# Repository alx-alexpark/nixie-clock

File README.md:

# ИН-12 Nixie Tube Clock

A nixie tube clock made using ИН-12 (IN-12) tubes. Uses k155id1 drivers and a boost converter made using [this reference design](https://github.com/drkmsmithjr/NixiePowerSupply). Time is synchronized over WiFi using NTP (<1sec inaccuracy), and all firmware is written using CircuitPython.

Read more at https://parkalex.dev/posts/nixieclock

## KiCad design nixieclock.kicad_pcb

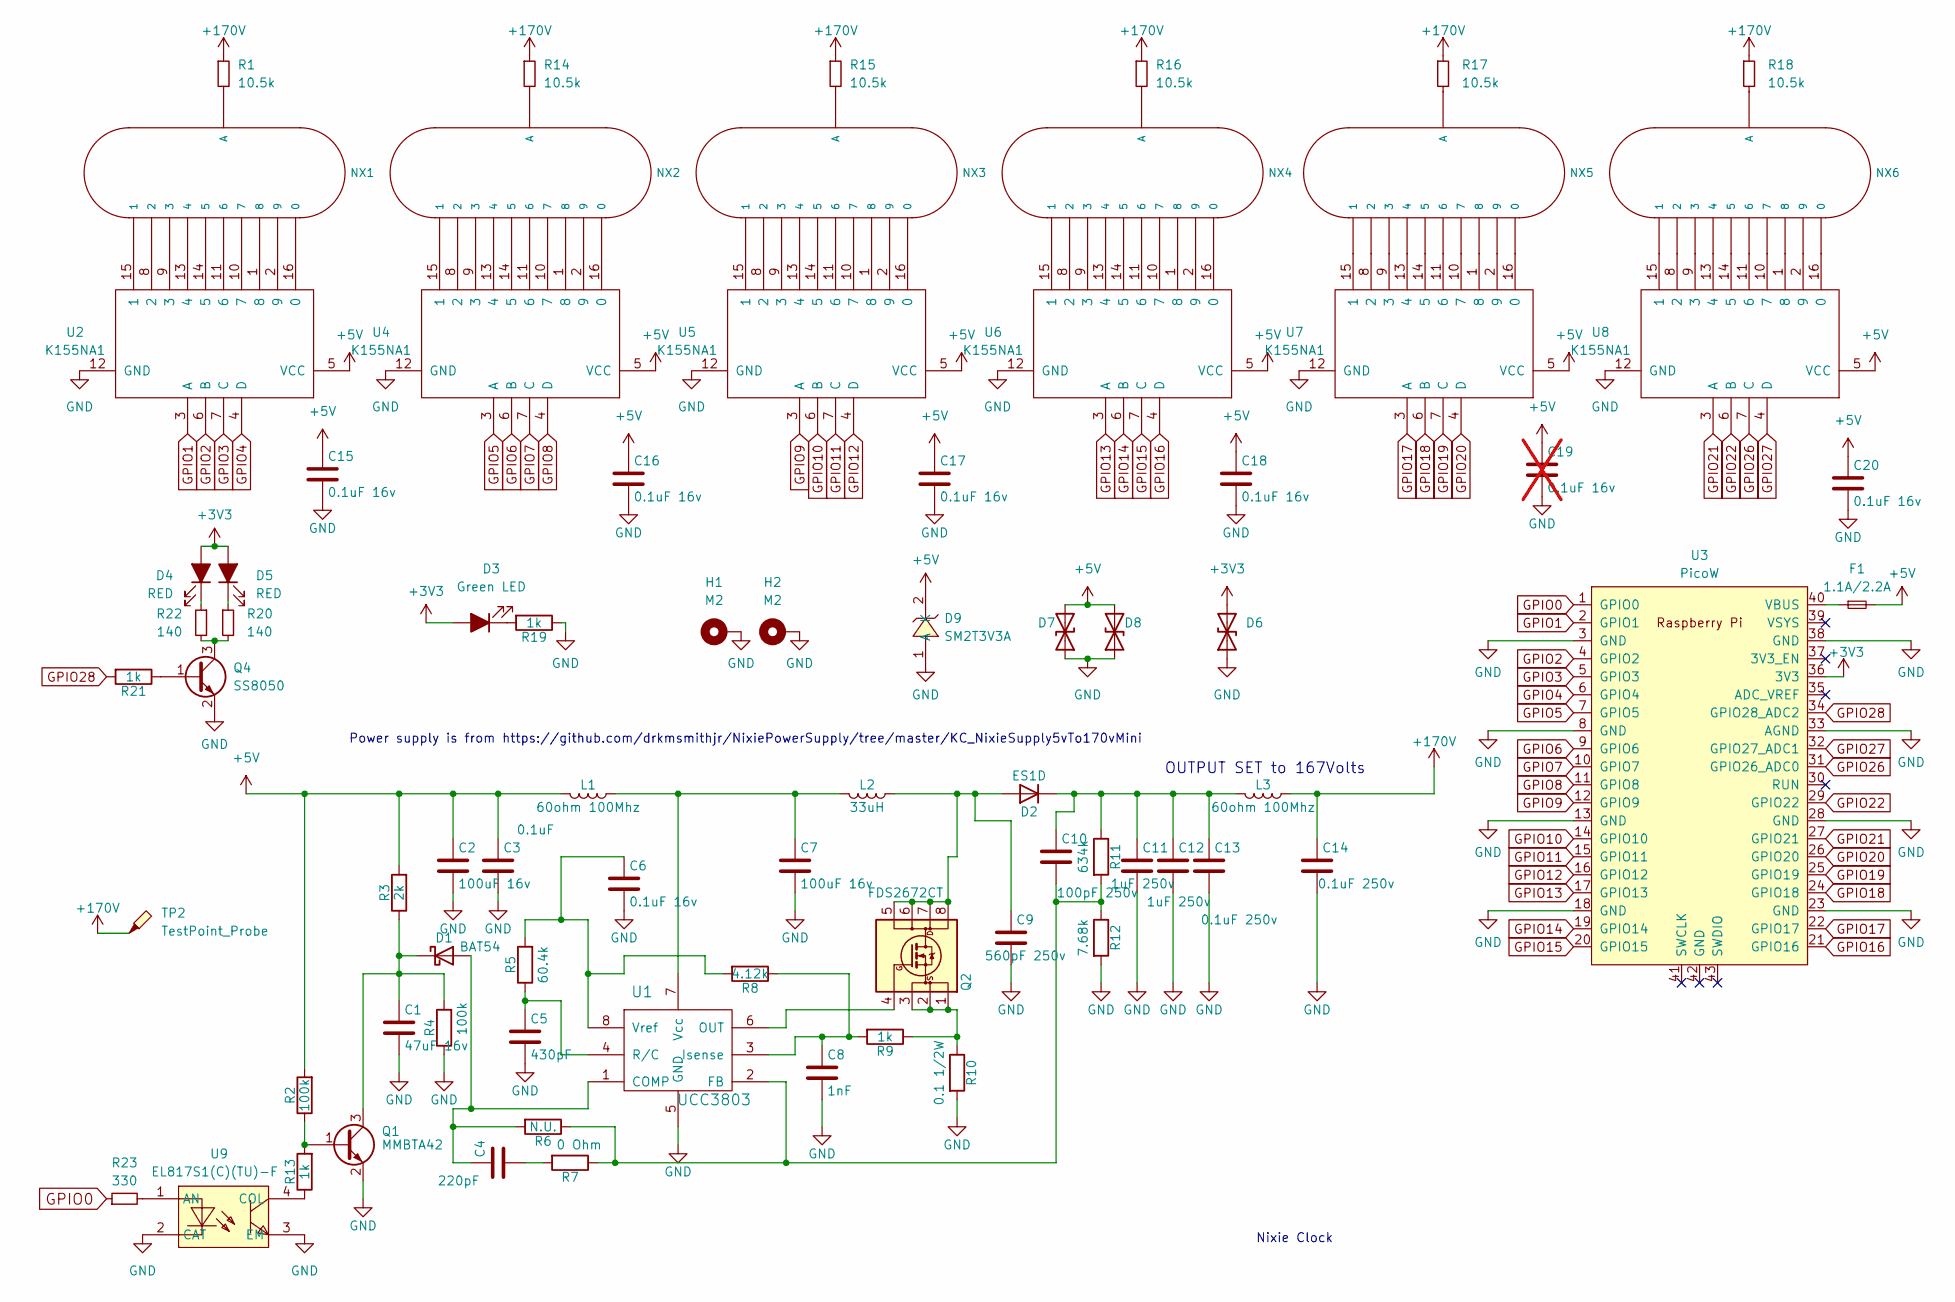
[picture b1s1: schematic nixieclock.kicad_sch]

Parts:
C1: 47uF 16v; C_1210_3225Metric_Pad1.33x2.70mm_HandSolder; LCSC Part C77101
C2, C7: 100uF 16v; C_1210_3225Metric_Pad1.33x2.70mm_HandSolder; LCSC Part C7432790
C3: 0.1uF; C_0603_1608Metric_Pad1.08x0.95mm_HandSolder; LCSC Part C14663
C4: 220pF; C_0402_1005Metric_Pad0.74x0.62mm_HandSolder; LCSC Part C1530
C5: 430pF; C_0805_2012Metric_Pad1.18x1.45mm_HandSolder; LCSC Part C67898
C6, C15, C16, C17, C18, C20: 0.1uF 16v; C_0603_1608Metric_Pad1.08x0.95mm_HandSolder; LCSC Part C14663
C8: 1nF; C_0603_1608Metric_Pad1.08x0.95mm_HandSolder; LCSC Part C100040
C9: 560pF 250v; C_0805_2012Metric_Pad1.18x1.45mm_HandSolder; LCSC Part C576987
C10: 100pF 250v; C_0805_2012Metric_Pad1.18x1.45mm_HandSolder; LCSC Part C5186766
C11, C12: 1uF 250v; C_1812_4532Metric_Pad1.57x3.40mm_HandSolder; LCSC Part C381468
C13, C14: 0.1uF 250v; C_0805_2012Metric_Pad1.18x1.45mm_HandSolder; LCSC Part C5182461
C19: 0.1uF 16v; C_0603_1608Metric_Pad1.08x0.95mm_HandSolder; LCSC Part C14663; not fitted
D1: BAT54; D_SOD-323_HandSoldering; MPN BAT54WS-7-F; LCSC Part C124205
D2: ES1D; D_SMA_Handsoldering; MPN ES1D; LCSC Part C84602
D3: Green LED; LED_0805_2012Metric_Pad1.15x1.40mm_HandSolder; LCSC Part C2297
D4, D5: RED; LED_0805_2012Metric_Pad1.15x1.40mm_HandSolder; LCSC Part C84256
D6, D7, D8: PESD5V5C1BLYL; D_SOD-882; MPN PESD5V5C1BLYL
D9: SM2T3V3A; DO-216AA_L1.9-W1.9-LS3.8-FD; LCSC Part C970557
F1: 1.1A/2.2A; Fuse_1812_4532Metric_Pad1.30x3.40mm_HandSolder; MPN MF-MSMF110-2
H1, H2: M2; MountingHole_2.2mm_M2_DIN965_Pad_TopBottom
L1, L3: 60ohm 100Mhz; L_0805_2012Metric_Pad1.05x1.20mm_HandSolder; MPN MH2029-600Y
L2: 33uH; WE-PD_1210; MPN 7447709330
NX1, NX2, NX3, NX4, NX5, NX6: IN-12A; nixies-us-IN-12-DSUB
Q1: MMBTA42; SOT-23_Handsoldering; LCSC Part C118745
Q2: FDS2672CT; SOIC-8_3.9x4.9mm_P1.27mm; MPN FDS2672CT-ND
Q4: SS8050; SOT-23
R1, R14, R15, R16, R17, R18: 10.5k; R_0805_2012Metric_Pad1.20x1.40mm_HandSolder; LCSC Part C2093736
R2, R4: 100k; R_0603_1608Metric_Pad0.98x0.95mm_HandSolder; LCSC Part C14675
R3: 2k; R_0603_1608Metric_Pad0.98x0.95mm_HandSolder; LCSC Part C22975
R5: 60.4k; R_0603_1608Metric_Pad0.98x0.95mm_HandSolder; LCSC Part C23089
R6: N.U.
R7: 0 Ohm; R_0603_1608Metric_Pad0.98x0.95mm_HandSolder; LCSC Part C21189
R8: 4.12k; R_0603_1608Metric_Pad0.98x0.95mm_HandSolder; LCSC Part C2960702
R9, R13, R19, R21: 1k; R_0603_1608Metric_Pad0.98x0.95mm_HandSolder; LCSC Part C21190
R10: 0.1 1/2W; C_1210_3225Metric_Pad1.33x2.70mm_HandSolder; LCSC Part C2974119
R11: 634k; R_1206_3216Metric_Pad1.30x1.75mm_HandSolder; LCSC Part C3037408
R12: 7.68k; R_1206_3216Metric_Pad1.30x1.75mm_HandSolder; LCSC Part C3037264
R20, R22: 140; R_0603_1608Metric_Pad0.98x0.95mm_HandSolder; LCSC Part C2974027
R23: 330; R_0603_1608Metric_Pad0.98x0.95mm_HandSolder; LCSC Part C23138
TP2: TestPoint_Probe; TestPoint_Loop_D2.54mm_Drill1.5mm_Beaded
U1: UCC3803; SOIC-8_3.9x4.9mm_P1.27mm; LCSC Part C2657971
U2, U4, U5, U6, U7, U8: K155NA1; DIP-16_W7.62mm_LongPads
U3: PicoW; RPi_PicoW_SMD_TH
U9: EL817S1(C)(TU)-F; OPTO-SMD-4_L4.6-W6.5-P2.54-LS10.3-TL; LCSC Part C106900

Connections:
+3V3: D3.2 (A), D4.2 (A), D5.2 (A), D6.2 (A2), U3.36 (3V3)
+5V: C2.1, C3.1, C15.1, C16.1, C17.1, C18.1, C19.1, C20.1, D7.2 (A2), D8.2 (A2), D9.2 (K), F1.2, L1.2, R2.2, R3.2, U2.5 (VCC), U4.5 (VCC), U5.5 (VCC), U6.5 (VCC), U7.5 (VCC), U8.5 (VCC)
+170V: C14.1, L3.1, R1.1, R14.1, R15.1, R16.1, R17.1, R18.1, TP2.1
GND: C1.2, C2.2, C3.2, C5.2, C6.2, C7.2, C8.2, C9.2, C11.2, C12.2, C13.2, C14.2, C15.2, C16.2, C17.2, C18.2, C19.2, C20.2, D6.1 (A1), D7.1 (A1), D8.1 (A1), D9.1 (A), H1.1, H2.1, Q1.2 (E), Q4.2 (E), R4.1, R10.2, R12.2, R19.1, U1.5 (GND), U2.12 (GND), U3.3 (GND), U3.8 (GND), U3.13 (GND), U3.18 (GND), U3.23 (GND), U3.28 (GND), U3.33 (AGND), U3.38 (GND), U4.12 (GND), U5.12 (GND), U6.12 (GND), U7.12 (GND), U8.12 (GND), U9.2 (CAT), U9.3 (EM)
GPIO0: R23.1, U3.1 (GPIO0)
GPIO1: U2.3 (A), U3.2 (GPIO1)
GPIO2: U2.6 (B), U3.4 (GPIO2)
GPIO3: U2.7 (C), U3.5 (GPIO3)
GPIO4: U2.4 (D), U3.6 (GPIO4)
GPIO5: U3.7 (GPIO5), U4.3 (A)
GPIO6: U3.9 (GPIO6), U4.6 (B)
GPIO7: U3.10 (GPIO7), U4.7 (C)
GPIO8: U3.11 (GPIO8), U4.4 (D)
GPIO9: U3.12 (GPIO9), U5.3 (A)
GPIO10: U3.14 (GPIO10), U5.6 (B)
GPIO11: U3.15 (GPIO11), U5.7 (C)
GPIO12: U3.16 (GPIO12), U5.4 (D)
GPIO13: U3.17 (GPIO13), U6.3 (A)
GPIO14: U3.19 (GPIO14), U6.6 (B)
GPIO15: U3.20 (GPIO15), U6.7 (C)
GPIO16: U3.21 (GPIO16), U6.4 (D)
GPIO17: U3.22 (GPIO17), U7.3 (A)
GPIO18: U3.24 (GPIO18), U7.6 (B)
GPIO19: U3.25 (GPIO19), U7.7 (C)
GPIO20: U3.26 (GPIO20), U7.4 (D)
GPIO21: U3.27 (GPIO21), U8.3 (A)
GPIO22: U3.29 (GPIO22), U8.6 (B)
GPIO26: U3.31 (GPIO26_ADC0), U8.7 (C)
GPIO27: U3.32 (GPIO27_ADC1), U8.4 (D)
GPIO28: R21.2, U3.34 (GPIO28_ADC2)
unnamed: C4.2, R7.2
unnamed: C4.1, D1.2 (A), R6.2, U1.1 (COMP)
unnamed: C1.1, D1.1 (K), Q1.3 (C), R3.1, R4.2
unnamed: C9.1, D2.2 (A), L2.1, Q2.5 (D), Q2.6 (D), Q2.7 (D), Q2.8 (D)
unnamed: C10.1, C11.1, C12.1, C13.1, D2.1 (K), L3.2, R11.1
unnamed: D3.1 (K), R19.2
unnamed: D4.1 (K), R22.1
unnamed: D5.1 (K), R20.1
unnamed: NX1.A, R1.2
unnamed: NX2.A, R14.2
unnamed: NX3.A, R15.2
unnamed: NX4.A, R16.2
unnamed: NX5.A, R17.2
unnamed: NX6.A, R18.2
unnamed: Q1.1 (B), R2.1, R13.2
unnamed: Q2.4 (G), U1.6 (OUT)
unnamed: Q2.1 (S), Q2.2 (S), Q2.3 (S), R9.1, R10.1
unnamed: Q4.1 (B), R21.1
unnamed: Q4.3 (C), R20.2, R22.2
unnamed: C10.2, R6.1, R7.1, R11.2, R12.1, U1.2 (FB)
unnamed: C8.1, R8.1, R9.2, U1.3 (Isense)
unnamed: C5.1, R5.1, U1.4 (R/C)
unnamed: C7.1, L1.1, L2.2, U1.7 (Vcc)
unnamed: C6.1, R5.2, R8.2, U1.8 (Vref)
unnamed: NX1.0, U2.16 (0)
unnamed: NX1.1, U2.15 (1)
unnamed: NX1.2, U2.8 (2)
unnamed: NX1.3, U2.9 (3)
unnamed: NX1.4, U2.13 (4)
unnamed: NX1.5, U2.14 (5)
unnamed: NX1.6, U2.11 (6)
unnamed: NX1.7, U2.10 (7)
unnamed: NX1.8, U2.1 (8)
unnamed: NX1.9, U2.2 (9)
unnamed: F1.1, U3.40 (VBUS)
unnamed: NX2.0, U4.16 (0)
unnamed: NX2.1, U4.15 (1)
unnamed: NX2.2, U4.8 (2)
unnamed: NX2.3, U4.9 (3)
unnamed: NX2.4, U4.13 (4)
unnamed: NX2.5, U4.14 (5)
unnamed: NX2.6, U4.11 (6)
unnamed: NX2.7, U4.10 (7)
unnamed: NX2.8, U4.1 (8)
unnamed: NX2.9, U4.2 (9)
unnamed: NX3.0, U5.16 (0)
unnamed: NX3.1, U5.15 (1)
unnamed: NX3.2, U5.8 (2)
unnamed: NX3.3, U5.9 (3)
unnamed: NX3.4, U5.13 (4)
unnamed: NX3.5, U5.14 (5)
unnamed: NX3.6, U5.11 (6)
unnamed: NX3.7, U5.10 (7)
unnamed: NX3.8, U5.1 (8)
unnamed: NX3.9, U5.2 (9)
unnamed: NX4.0, U6.16 (0)
unnamed: NX4.1, U6.15 (1)
unnamed: NX4.2, U6.8 (2)
unnamed: NX4.3, U6.9 (3)
unnamed: NX4.4, U6.13 (4)
unnamed: NX4.5, U6.14 (5)
unnamed: NX4.6, U6.11 (6)
unnamed: NX4.7, U6.10 (7)
unnamed: NX4.8, U6.1 (8)
unnamed: NX4.9, U6.2 (9)
unnamed: NX5.0, U7.16 (0)
unnamed: NX5.1, U7.15 (1)
unnamed: NX5.2, U7.8 (2)
unnamed: NX5.3, U7.9 (3)
unnamed: NX5.4, U7.13 (4)
unnamed: NX5.5, U7.14 (5)
unnamed: NX5.6, U7.11 (6)
unnamed: NX5.7, U7.10 (7)
unnamed: NX5.8, U7.1 (8)
unnamed: NX5.9, U7.2 (9)
unnamed: NX6.0, U8.16 (0)
unnamed: NX6.1, U8.15 (1)
unnamed: NX6.2, U8.8 (2)
unnamed: NX6.3, U8.9 (3)
unnamed: NX6.4, U8.13 (4)
unnamed: NX6.5, U8.14 (5)
unnamed: NX6.6, U8.11 (6)
unnamed: NX6.7, U8.10 (7)
unnamed: NX6.8, U8.1 (8)
unnamed: NX6.9, U8.2 (9)
unnamed: R23.2, U9.1 (AN)
unnamed: R13.1, U9.4 (COL)

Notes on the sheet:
Power supply is from https://github.com/drkmsmithjr/NixiePowerSupply/tree/master/KC_NixieSupply5vTo170vMini
Nixie Clock
OUTPUT SET to 167Volts

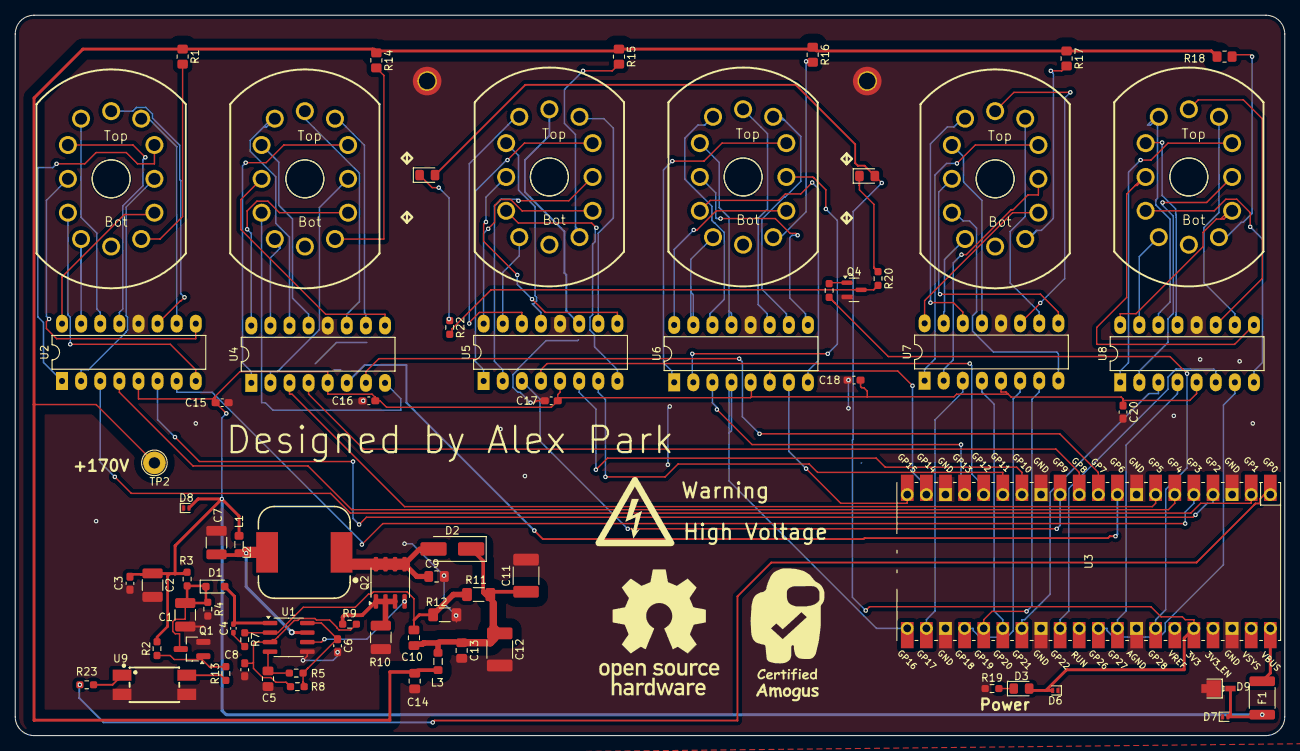
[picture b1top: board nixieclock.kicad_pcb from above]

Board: 2 copper layers, 168.8 x 95.8 mm, 75 parts (0 on the bottom side), 117 nets.

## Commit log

2024-12-15 things happened
2024-12-15 schematic mostly done, started laying out board
2024-12-15 layout
2024-12-15 mostly done i guess?
2024-12-16 Finishing touches to pcb
2024-12-16 remove pdf
2024-12-16 updates to silk screen
2024-12-17 small modifications to pcb
2024-12-17 more random things
2024-12-17 Had the footprints for nixies completely wrong, redid them
2024-12-17 added clearances for safety on hv nets
2024-12-18 add tvs diodes for protection
2024-12-18 increase board size
2024-12-20 final order
